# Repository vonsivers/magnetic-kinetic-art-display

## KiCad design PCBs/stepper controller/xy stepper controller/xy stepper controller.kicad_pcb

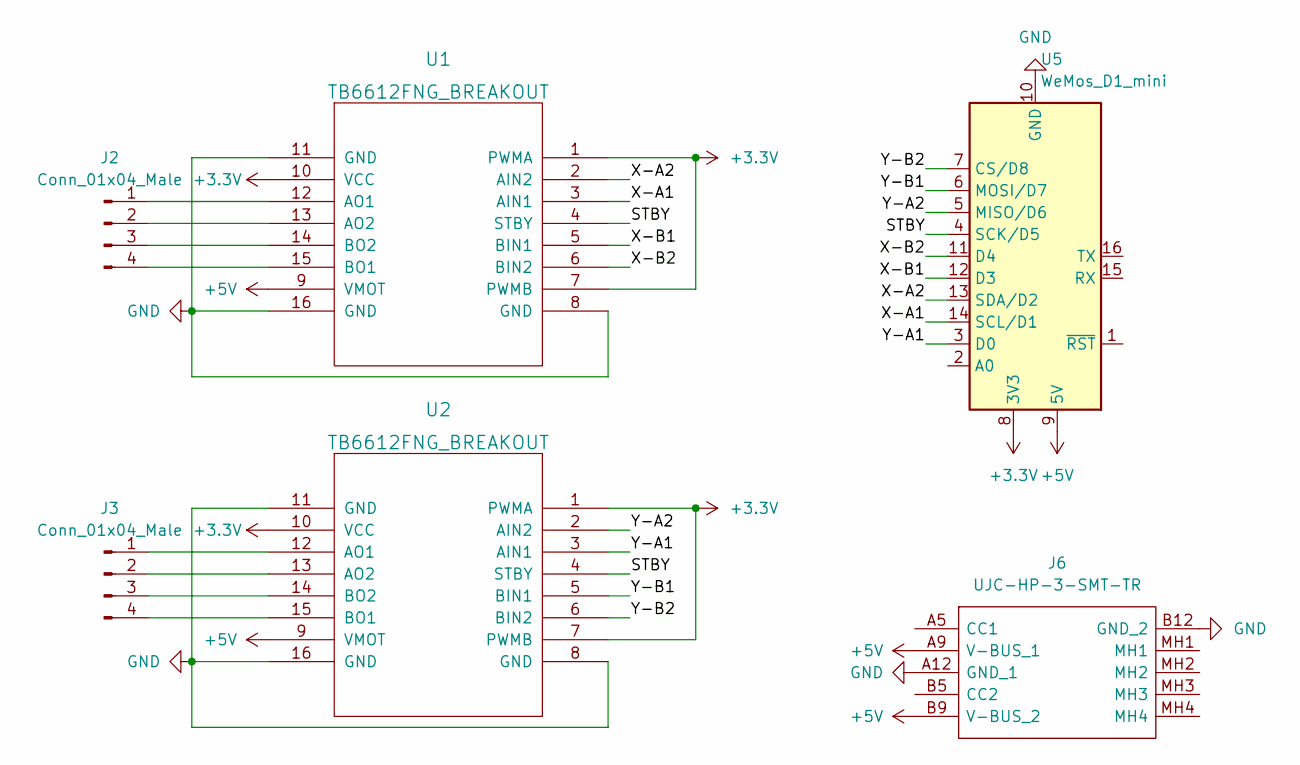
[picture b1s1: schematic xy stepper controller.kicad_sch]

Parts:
J2, J3: Conn_01x04_Male; JST_XH_B4B-XH-AM_1x04_P2.50mm_Vertical
J6: UJC-HP-3-SMT-TR; UJCHP3SMTTR; Manufacturer_Part_Number UJC-HP-3-SMT-TR; Mouser Part Number 490-UJC-HP-3-SMT-TR
U1, U2: TB6612FNG_BREAKOUT; TB6612FNG_Breakout
U5: WeMos_D1_mini; WEMOS_D1_mini_light

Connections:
+3.3V: U1.1 (PWMA), U1.7 (PWMB), U1.10 (VCC), U2.1 (PWMA), U2.7 (PWMB), U2.10 (VCC), U5.8 (3V3)
+5V: J6.A9 (V-BUS_1), J6.B9 (V-BUS_2), U1.9 (VMOT), U2.9 (VMOT), U5.9 (5V)
/STBY: U1.4 (STBY), U2.4 (STBY), U5.4 (SCK/D5)
/X-A1: U1.3 (AIN1), U5.14 (SCL/D1)
/X-A2: U1.2 (AIN2), U5.13 (SDA/D2)
/X-B1: U1.5 (BIN1), U5.12 (D3)
/X-B2: U1.6 (BIN2), U5.11 (D4)
/Y-A1: U2.3 (AIN1), U5.3 (D0)
/Y-A2: U2.2 (AIN2), U5.5 (MISO/D6)
/Y-B1: U2.5 (BIN1), U5.6 (MOSI/D7)
/Y-B2: U2.6 (BIN2), U5.7 (CS/D8)
GND: J6.A12 (GND_1), J6.B12 (GND_2), U1.8 (GND), U1.11 (GND), U1.16 (GND), U2.8 (GND), U2.11 (GND), U2.16 (GND), U5.10 (GND)
unnamed: J2.1, U1.12 (AO1)
unnamed: J2.2, U1.13 (AO2)
unnamed: J2.3, U1.14 (BO2)
unnamed: J2.4, U1.15 (BO1)
unnamed: J3.1, U2.12 (AO1)
unnamed: J3.2, U2.13 (AO2)
unnamed: J3.3, U2.14 (BO2)
unnamed: J3.4, U2.15 (BO1)

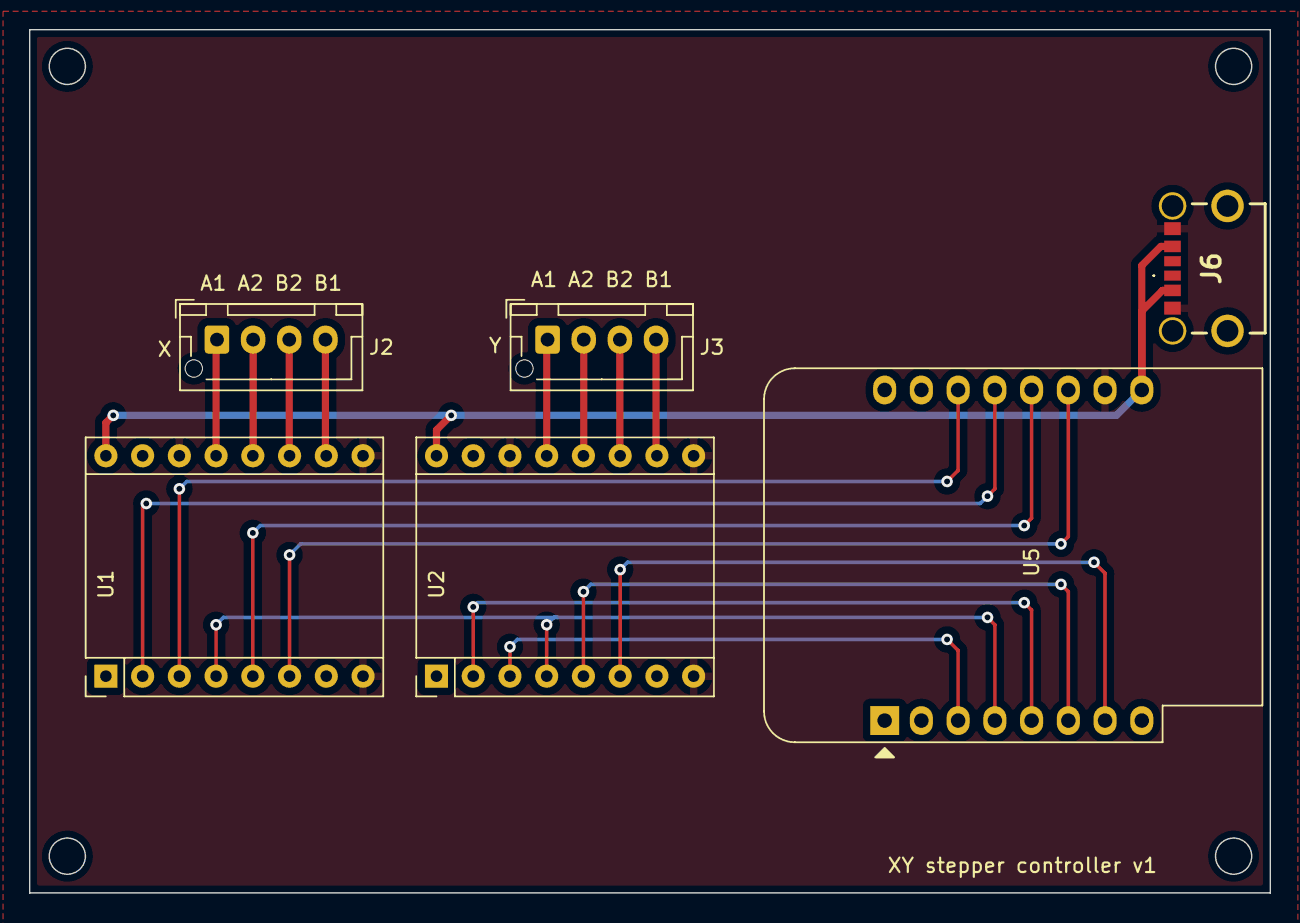
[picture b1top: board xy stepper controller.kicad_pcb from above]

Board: 2 copper layers, 85.8 x 59.7 mm, 6 parts (0 on the bottom side), 20 nets.

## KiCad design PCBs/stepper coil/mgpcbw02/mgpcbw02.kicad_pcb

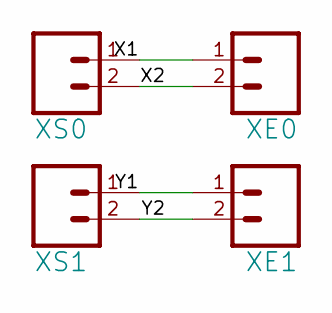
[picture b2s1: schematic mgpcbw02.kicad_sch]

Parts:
XE0, XE1: (no value)
XS0, XS1: (no value)

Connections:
X1: XE0.1, XS0.1
X2: XE0.2, XS0.2
Y1: XE1.1, XS1.1
Y2: XE1.2, XS1.2

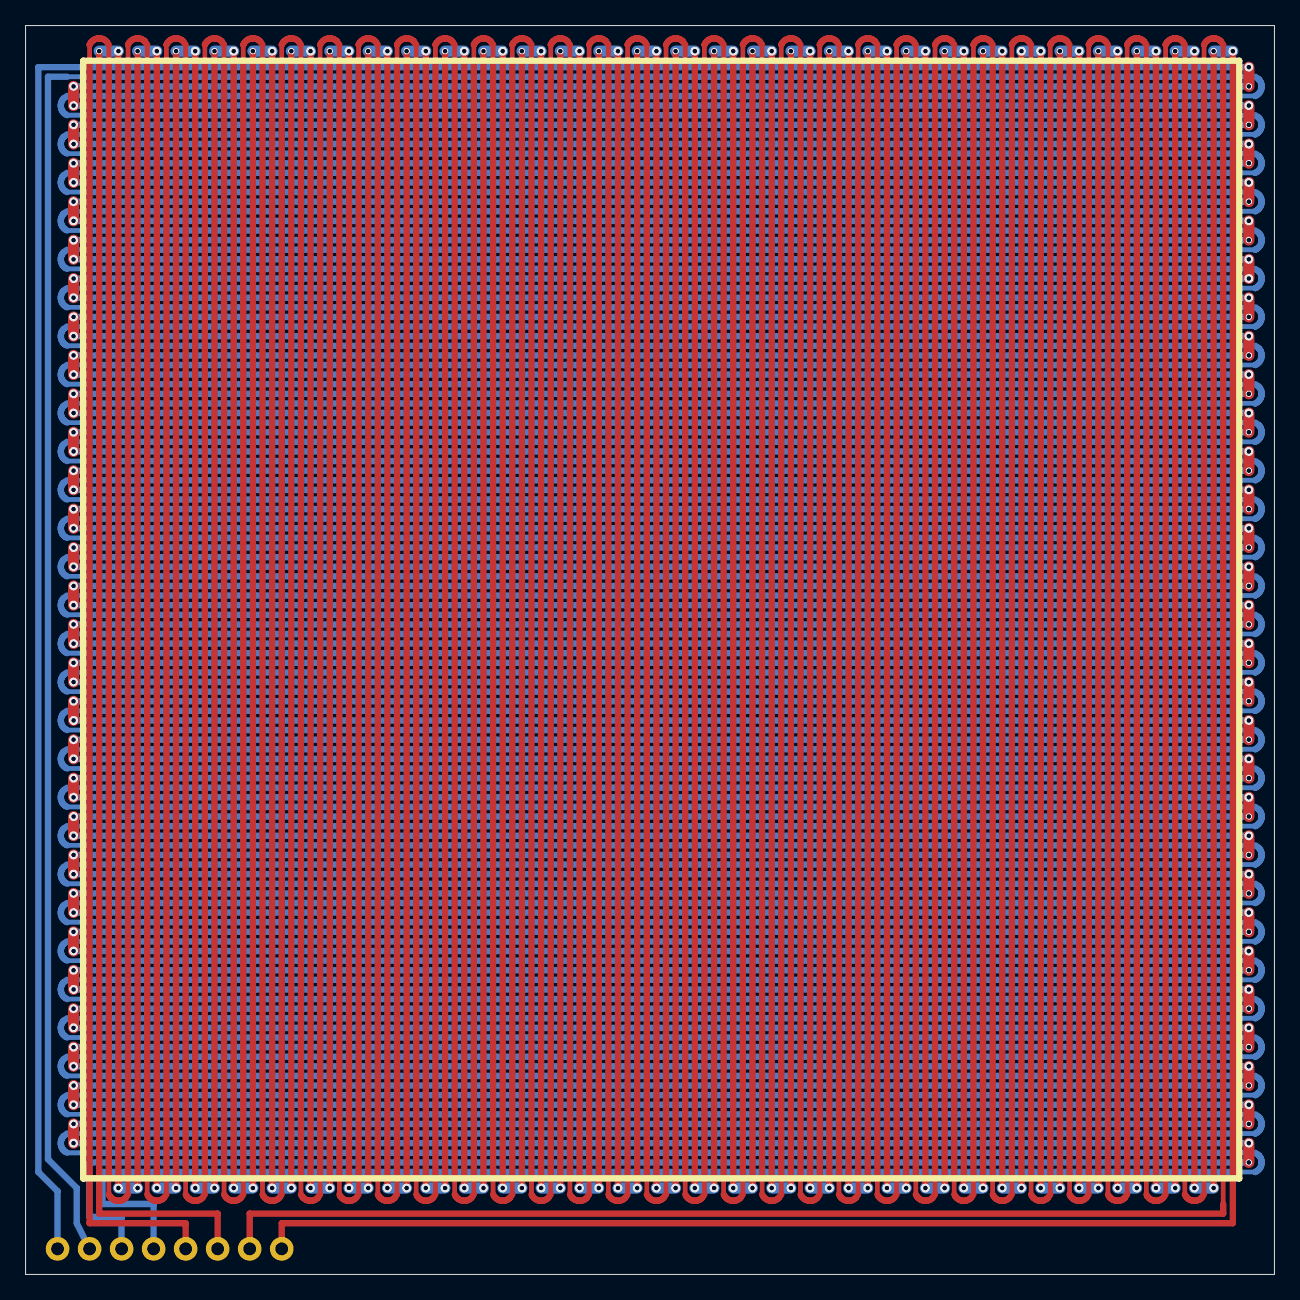
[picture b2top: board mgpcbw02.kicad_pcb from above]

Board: 2 copper layers, 99.1 x 99.1 mm, 4 parts (0 on the bottom side), 4 nets.

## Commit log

2023-03-04 init
